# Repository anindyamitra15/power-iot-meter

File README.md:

# Iot Enabled Power Meter
Client server model for real-time monitoring of power usage aimed to simplify and modernise power usage readings and subsequent billing. Server backend handled by Firebase and Frontend made as a dynamic web app with angular framework. This project aims to elevate the process of power metering to modern connected standards and is primarily aimed towards power utility companies such that they may modernise their metering devices and enable them to be connected to the internet, allowing realtime monitoring and other advanced features like automated billing, remote disconnection, power outage detection and much more!  
The primary focus points of this project is simplicity, ease of installation of module, cost efficiency and rich user experience. 

## Documentation:
Slideshow presentation of the project highlighting the prominent topics discussed is available [here](https://docs.google.com/presentation/d/1IoBsD3WG-SK9_eWFI1Uqt-yPBRw3dVxrFmFgWGnbJ7E/edit?usp=sharing).  
The [documentation](https://docs.google.com/document/d/1lsBinQPk2TXrA8E3_NlRT1Esq-xPcBFSQFjI79IAyAw/edit?usp=sharing) for the research conducted and subsequent issues addressed has been made available.  
[Dataflow logic](https://whimsical.com/data-flow-XnRbm9PbMYaVgHn5g6pd81) and [Firmware Algorithm Logic](https://whimsical.com/firmware-algorithm-PJ4HBDd6Cb4NwG5o3SaENn) flowcharts are also provided.
Project Term Paper available [here](https://docs.google.com/document/d/1HhWOn-NgjPpBc6PuhfizeNlCIJG0mVvy1hvxCMSfRlQ/edit?usp=sharing).  
Short Infographic video showcasing the project and primary discussion points is available [here](https://www.youtube.com/watch?v=jMkZ5F2Xh4k)

## Folder Structure:
```
./
  |-- power-iot-meter-fe (the frontend dashboard)
  --- power-iot-meter-hw (the firmware sketch)
```

## Tools used:
- Angular
- Platform IO
- Espressif ESP32
- Arduino Framework
- Firebase RTDB
- Firebase Auth
- KiCAD

## Languages Used: 
- C/C++
- JS/TS

## Members:
- Arnab Das - [@arnabdas01](https://github.com/arnabdas01) 
- Anindya Kanti Mitra - [@anindyamitra15](https://github.com/anindyamitra15) 
- Rishav Dutta - [@randomdelta6](https://github.com/RandomDelta6) 
- Anubhav Dutta - [@anubhav666](https://github.com/anubhav666)

## Acknowledgement:
- This project has been developed under the guidance of [Dr. Bandana Barman](https://kgec.edu.in/department?name=ece).

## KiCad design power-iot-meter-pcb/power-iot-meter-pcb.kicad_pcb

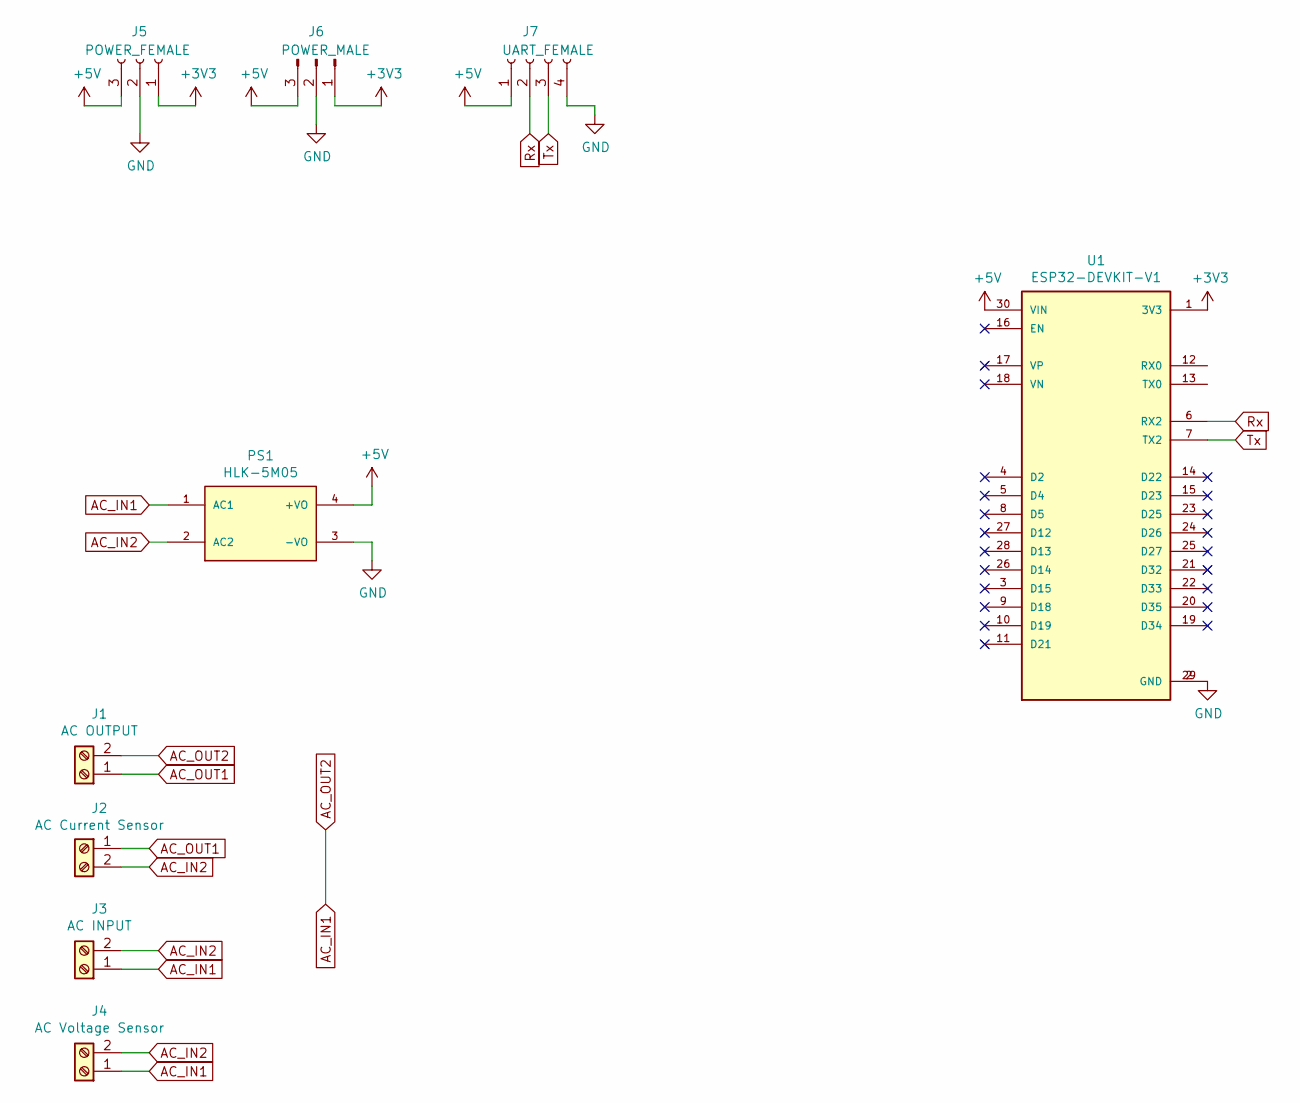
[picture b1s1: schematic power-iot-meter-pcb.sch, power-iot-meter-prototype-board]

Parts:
J1: AC OUTPUT; TerminalBlock_Altech_AK300-2_P5.00mm
J2: AC Current Sensor; SolderWire-0.5sqmm_1x02_P4.6mm_D0.9mm_OD2.1mm_Relief
J3: AC INPUT; TerminalBlock_Altech_AK300-2_P5.00mm
J4: AC Voltage Sensor; SolderWire-0.5sqmm_1x02_P4.6mm_D0.9mm_OD2.1mm_Relief
J5: POWER_FEMALE; PinSocket_1x03_P2.00mm_Vertical
J6: POWER_MALE; PinHeader_1x03_P2.00mm_Vertical
J7: UART_FEMALE; PinSocket_1x04_P2.00mm_Vertical
PS1: HLK-5M05; CONV_HLK-5M05; PARTREV N/A
U1: ESP32-DEVKIT-V1; MODULE_ESP32_DEVKIT_V1; PARTREV N/A

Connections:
+3V3: J5.1, J6.1, U1.1 (3V3)
+5V: J5.3, J6.3, J7.1, PS1.4 (+VO), U1.30 (VIN)
AC_IN1: J1.2, J3.1, J4.1, PS1.1 (AC1)
AC_IN2: J2.2, J3.2, J4.2, PS1.2 (AC2)
AC_OUT1: J1.1, J2.1
GND: J5.2, J6.2, J7.4, PS1.3 (-VO), U1.2 (GND), U1.29 (GND)
Rx: J7.2, U1.6 (RX2)
Tx: J7.3, U1.7 (TX2)

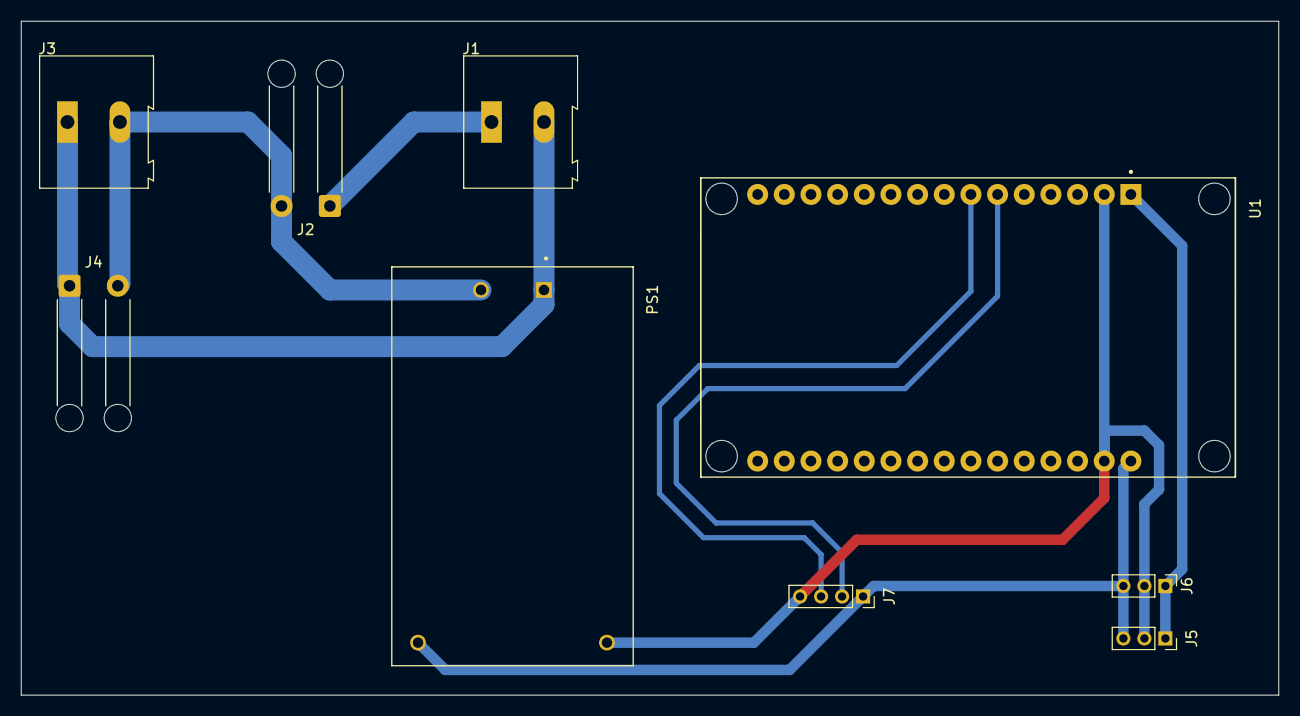
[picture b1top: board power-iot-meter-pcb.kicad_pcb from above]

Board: 2 copper layers, 119.8 x 64.2 mm, 9 parts (0 on the bottom side), 8 nets.

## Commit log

2022-05-06 file functions added
2022-05-06 init file system function update
2022-05-07 added webpages for wifimanagement
2022-05-07 webpage hosted from SPIFFS successfully
2022-05-07 pushed changes so far
2022-05-07 AP list configured
2022-05-08 added table render jquery
2022-05-09 webpage side done
2022-05-09 try in ap mode
2022-05-09 added safety on scanAps function, wifi connects to station in code
2022-05-09 yet to be tested
2022-05-10 major refactoring
2022-05-10 tested
2022-05-11 works ❤
2022-05-11 cleaned
2022-05-12 pass check implemented, works ♥
2022-05-12 minified files
2022-05-12 minor changes
2022-05-12 added util functions, added firebase
2022-05-19 fetch/retrive data from firebase works
2022-05-21 updated to store uid to storage after login
2022-05-21 updated fetchData to return in string format for more flexibility
2022-05-27 pushing broken changes
2022-05-30 timing.h filled
2022-05-30 updated gmt offset
2022-06-03 major changes: implemented firebase and firebase-auth
2022-06-05 footer and nav implemented
2022-06-05 ui layout working
2022-06-06 before writing module/raw hw files
2022-06-06 user can see his/her device's data in real-time
2022-06-11 timestamp can be obtained properly
2022-06-11 test data uploading works
2022-06-11 added PCB layout
2022-06-11 added page description
2022-06-12 Implement HardwarePropModule
2022-06-12 PCB update
2022-06-13 added frequency and power factor support
2022-06-13 production budget motified
2022-06-13 improved table styling
2022-06-13 updated packet struct
2022-06-13 changed angular.json budget
2022-06-14 cghanges in schematic orientation
2022-09-18 updated 'tools used' section
2022-10-20 power cut detection working
2023-08-22 Bump protobufjs from 6.11.3 to 6.11.4 in /power-iot-meter-fe
    Bumps [protobufjs](https://github.com/protobufjs/protobuf.js) from 6.11.3 to 6.11.4.
    - [Release notes](https://github.com/protobufjs/protobuf.js/releases)
    - [Changelog](https://github.com/protobufjs/protobuf.js/blob/master/CHANGELOG.md)
    - [Commits](https://github.com/protobufjs/protobuf.js/commits)
    ---
    updated-dependencies:
